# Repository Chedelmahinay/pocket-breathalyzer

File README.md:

# iot-project

### Conventional Commits

In this project, **Conventional Commits** are used, which is a simple set of rules to structure and create an explicit commit history that is easy to read both for humans and machines if needed.

Learn more about describing the features, fixes, and breaking changes made in commit messages here: [Click Me](https://www.conventionalcommits.org/en/v1.0.0/#specification)

#### The commit message should be structured as follows:
```<type>(scope): <description>```

#### The commit contains the following structural elements:

- **fix**: a commit of the ```type``` ___fix___ patches a bug in your codebase.

- **feat**: a commit of the ```type``` ___feat___ introduces a new feature to the codebase.

- **!**: a commit that appends a ___!___ after the ```scope```, introduces a ___breaking change___. A breaking change can be part of commits of any type.

#### Examples:

Commit message with ```!``` to draw attention to a ___breaking change___:

- ```feat(api)!: send an email to the customer when a product is shipped```

Commit message with ```scope``` lang:

- ```feat(lang): add Polish language```

Commit message with ```type``` fix:

- ```fix(ui): css syntax error```

### Branching Strategy

A **branching strategy** is a set of rules or guidelines that development teams use to manage the process of writing, merging, and deploying code with the help of a version control system like **Git**. It defines how developers interact with a shared codebase.

Strategies like these are essential as they help in keeping project repositories organized, error-free, and **avoid the unwanted merge conflicts** when multiple developers simultaneously push and pull code from the same repository.

To learn more about branching strategies: [Click Me](https://www.geeksforgeeks.org/git/branching-strategies-in-git/)

A _modified_ version of the **GitLab Flow** is used in this project.

#### GitLab Flow (modified):

The types of branches that can be present in GitFlow are:

- **master/main**: Main production branch housing stable release ready code.

- **dev**: Contains new features and bug fixes. This branch is used to combine new features and bug fixes for the release. Upon completion, developers merge the changes from the ```dev``` branch into the ```main/master``` branches.

- **feature/<scope<d>>**: Developers initiate ```feature/*``` branch from the ```dev``` branch to implement new features or address bugs. Upon completion, they integrate the changes from the ```feature/*``` branch into the ```dev``` branch. **For example:**
    - ```feature/ui```: To work on the UI of the project
    - ```feature/api```: To work on the API calls of the project

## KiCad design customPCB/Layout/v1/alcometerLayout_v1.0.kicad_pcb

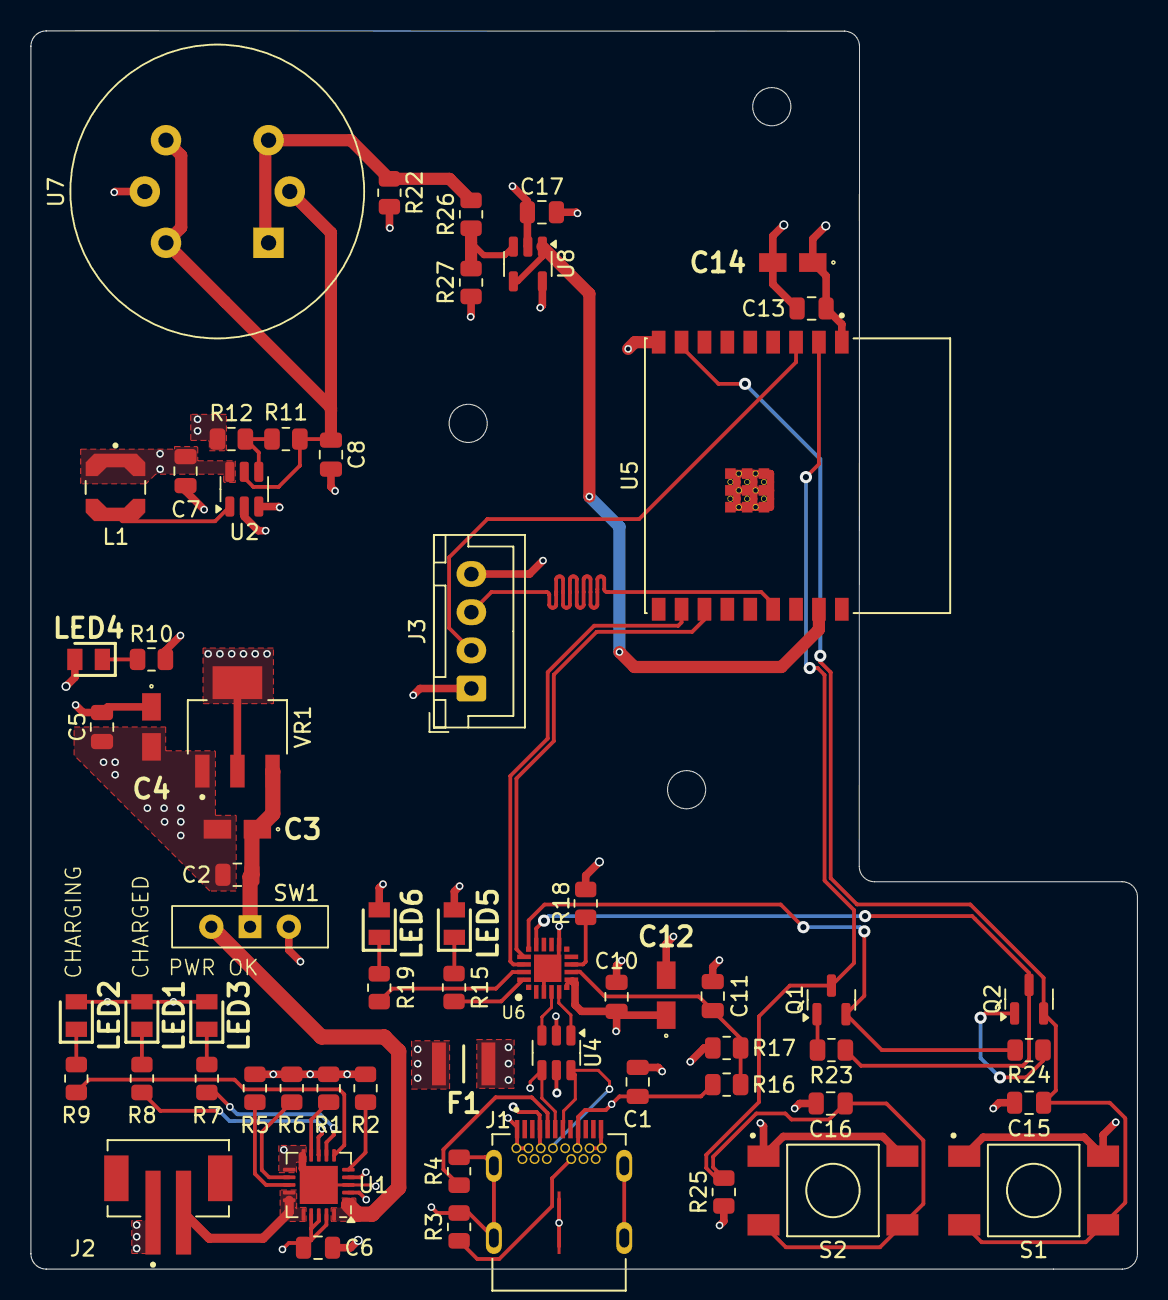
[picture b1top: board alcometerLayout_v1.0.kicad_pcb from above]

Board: 4 copper layers, 72.5 x 81.1 mm, 63 parts (0 on the bottom side), 44 nets.

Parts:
C1, C2, C5, C10, C13, C15: 0.1uF; C_0805_2012Metric
C3, C4, C14: 10uF; T491A
C6, C11, C16: 1uF; C_0805_2012Metric
C7: 4.7uF; C_0805_2012Metric
C8: 10uF; C_0805_2012Metric
C12: 4.7uF; T491A
C17: 100nF; C_0805_2012Metric
F1: 0ZCH0110AF2E; FUSC3226X100N
J1: SS-52400-003; BELFUSE_SS-52400-003
J2: B2B-PH-SM4-TB; JST_B2B-PH-SM4-TB
J3: Conn_01x04_Pin; JST_XH_B4B-XH-A_1x04_P2.50mm_Vertical
L1: 4.7uH; IND_LPS4018-472MRC
LED1, LED5: LTST-C170GKT; LEDC2012X120N
LED2, LED4, LED6: LTST-C170KRKT; LEDC2012X120N
LED3: LTST-C170TBKT; LEDC2012X120N
Q1, Q2: BC817; SOT-23
R1, R2, R23, R24, R25, R27: 10K; R_0805_2012Metric
R3, R4, R26: 5K1; R_0805_2012Metric
R5: 2K; R_0805_2012Metric
R6: 20K; R_0805_2012Metric
R7, R8, R9, R10, R15, R19: 470; R_0805_2012Metric
R11: 976; R_0805_2012Metric
R12: 309; R_0805_2012Metric
R16: 22K1; R_0805_2012Metric
R17: 47K5; R_0805_2012Metric
R18, R22: 1K; R_0805_2012Metric
S1, S2: FSM4JSMAATR; SW_FSM4JSMAATR
SW1: SW_Wuerth_450301014042; SW_Slide-03_Wuerth-WS-SLTV_10x2.5x6.4_P2.54mm
U1: MCP73871; QFN-20-1EP_4x4mm_P0.5mm_EP2.5x2.5mm
U2: MCP1640Bx-xCHY; SOT-23-6
U4: USBLC6-2SC6; SOT-23-6
U5: ESP32-C3-WROOM-02-H4; MODULE_ESP32-C3-WROOM-02-H4
U6: CP2102N-A02-GQFN20; WFQFN-20
U7: MQ-3; MQ-6
U8: MCP6001R; SOT-23-5
VR1: LM1117MPX-3.3; VREG_LM1117MPX-3.3

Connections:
+3V3: C4.1, C5.1, C7.1, C10.1, C12.1, C13.1, C14.1, C17.1, J3.1, L1.1, LED4.2 (A), LED5.2 (A), LED6.2 (A), R18.1, R25.1, U2.3 (EN), U2.6 (V_{IN}), U5.1 (3V3), U6.6 (VDD), U6.7 (VREGIN), U8.2 (V+), VR1.2 (VOUT_2), VR1.4 (VOUT_4)
+5V: C2.1, C3.1, C8.1, R11.1, SW1.1 (B), SW1.3 (A), U1.1 (OUT), U1.20 (OUT), U2.5 (V_{OUT}), U7.2 (VH+), U7.4 (A2), U7.6 (A1), VR1.3 (VIN)
/+5V_USB: C6.1, F1.2, LED1.2 (A), LED2.2 (A), LED3.2 (A), U1.2 (VPCC), U1.4 (PROG2), U1.17 (CE), U1.18 (IN), U1.19 (IN)
/CHARGED: R8.1, U1.8 (STAT1/~LBO)
/CHARGING: R9.1, U1.6 (~PG)
/CHARGING_POWER_GOOD: R7.1, U1.7 (STAT2)
/ESP32-C6-MINI-1/+3V3_ADC: U5.17 (IO1), U8.1, U8.4 (-)
/ESP32-C6-MINI-1/BOOT: C15.1, Q2.2 (E), S1.3, S1.4, U5.8 (IO9)
/ESP32-C6-MINI-1/DTR: Q2.3 (C), R23.1, U6.15 (CTS)
/ESP32-C6-MINI-1/EN: C16.1, Q1.3 (C), R25.2, S2.3, S2.4, U5.2 (EN)
/ESP32-C6-MINI-1/RTS: Q1.2 (E), R24.1, U6.16 (RTS)
/ESP32-C6-MINI-1/RX_TX: U5.12 (TXD), U6.17 (RXD)
/ESP32-C6-MINI-1/SCL: J3.3, U5.15 (IO3)
/ESP32-C6-MINI-1/SDA: J3.2, U5.3 (IO4)
/ESP32-C6-MINI-1/Sensors/+5V_ADC: R22.1, R26.1, U7.1 (B1), U7.3 (B2)
/ESP32-C6-MINI-1/TX_RX: U5.11 (RXD), U6.18 (TXD)
/ESP32-C6-MINI-1/USB_D+: U4.3 (I/O2), U6.4 (D+)
/ESP32-C6-MINI-1/USB_D-: U4.1 (I/O1), U6.5 (D-)
/PWD_LED: LED4.1 (K), R10.2
/USB_DN: J1.A7 (DN1), J1.B7 (DN2), U4.6 (I/O1)
/USB_DP: J1.A6 (DP1), J1.B6 (DP2), U4.4 (I/O2)
/VBAT: J2.2, U1.14 (V_{BAT}), U1.15 (V_{BAT}), U1.16 (V_{BAT_SENSE})
/VBUS: C1.1, F1.1, J1.A4 (VBUSA1), J1.A9 (VBUSA2), J1.B4 (VBUSB1), J1.B9 (VBUSB2), R16.1, U4.5 (VBUS)
GND: C1.2, C2.2, C3.2, C4.2, C5.2, C6.2, C7.2, C8.2, C10.2, C11.2, C12.2, C13.2, C14.2, C15.2, C16.2, C17.2, J1.A1 (GNDA1), J1.A12 (GNDA2), J1.B1 (GNDB1), J1.B12 (GNDB2), J1.G1 (GND/SHIELD), J1.G2 (GND/SHIELD), J1.G3 (GND/SHIELD), J1.G4 (GND/SHIELD), J1.S1 (GND/SHIELD), J1.S2 (GND/SHIELD), J1.S3 (GND/SHIELD), J1.S4 (GND/SHIELD), J2.1, J3.4, R1.2, R2.2, R3.2, R4.2, R5.2, R6.2, R10.1, R12.2, R17.2, R22.2, R27.2, S1.1, S1.2, S2.1, S2.2, SW1.2 (C), U1.3 (SEL), U1.10 (V_{SS}), U1.11 (V_{SS}), U1.21 (V_{SS}), U2.2 (GND), U4.2 (GND), U5.9 (GND), U5.19 (GND), U5.20 (GND), U5.21 (GND), U5.22 (GND), U5.23 (GND), U5.24 (GND), U5.25 (GND), U5.26 (GND), U5.27 (GND), U5.28 (GND), U5.29 (GND), U5.30 (GND), U5.31 (GND), U5.32 (GND), U5.33 (GND), U5.34 (GND), U5.35 (GND), U5.36 (GND), U5.37 (GND), U5.38 (GND), U5.39 (GND), U6.3 (GND), U6.12 (GND), U6.EXP (GND), U7.5 (VH-), U8.5 (V-), VR1.1 (GND)
unnamed: J1.A5 (CC1), R4.1
unnamed: J1.B5 (CC2), R3.1
unnamed: LED1.1 (K), R8.2
unnamed: LED2.1 (K), R9.2
unnamed: LED3.1 (K), R7.2
unnamed: LED5.1 (K), R15.2
unnamed: LED6.1 (K), R19.2
unnamed: Q1.1 (B), R23.2
unnamed: Q2.1 (B), R24.2
unnamed: R5.1, U1.13 (PROG1)
unnamed: R6.1, U1.12 (PROG3)
unnamed: R2.1, U1.5 (THERM)
unnamed: R1.1, U1.9 (~TE)
unnamed: L1.2, U2.1 (SW)
unnamed: R11.2, R12.1, U2.4 (V_{FB})
unnamed: R15.1, U6.20 (GPIO2/TXT)
unnamed: R19.1, U6.19 (GPIO3/RXT)
unnamed: R18.2, U6.9 (RSTB)
unnamed: C11.1, R16.2, R17.1, U6.8 (VBUS)
unnamed: R26.2, R27.1, U8.3 (+)

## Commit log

2025-11-11 fix(readme): change readme
2025-11-12 Configure SAST in `.gitlab-ci.yml`, creating this file if it does not already exist
2025-11-22 project creation and supabase connection
2025-11-25 Documentation(readme): Add Project overview and task scaling
2025-11-25 fix(gitignore): add .env.local
2025-11-25 package-lock.json
2025-11-30 feat(username): added username option to signup and updated it to be shown instead of email
2025-11-30 feat(ui): protectedPage initial commit
2025-12-11 feat(ble): BLE test
2025-12-16 feat(ui): landingPage initial commit + Hero section edited/in progress
2025-12-18 feat(ui): redesigned page + added user guide + project description
2025-12-22 modulated landingPage files + removed unused files + refactored margin/padding & text contents in section
2025-12-23 feat(idf): test ble w/ esp idf
2025-12-24 feat(ble): add barebone ble functionality
2025-12-28 feat(ble): add reconnection & manual disconnect & delete hello_world example
2025-12-28 vercel test
2025-12-28 Remove node_modules from repository
2025-12-28 Remove node_modules committed by mistake
2025-12-28 Removed deploy button
2025-12-28 chore: remove accidental root-level npm files
2025-12-28 test: Repo mirroring
2025-12-28 test: Repo
2025-12-29 modification: Modified settings for vercel
2025-12-29 update: Updated next for vercel
2026-01-04 feat(adc)!: barebone adc1 measuring w/ ble on
2026-01-04 fix(gitignore): gitignore fix lol
2026-01-11 feat(user info page): Added user info page. Modification possibility needs to be added and ui changes
2026-01-11 feat(user info page): vercel test
2026-01-12 feat(sensor): delete b profile(ble) & convert adc to bac & send bac to client
2026-01-14 fix(esp32): build files. must add them to .gitignore later
2026-01-14 fix(gitignore): add esp idf build files into .gitignore
2026-01-18 feat(display): rework OLED display and add SSD1306 driver with isolated RTOS task for test
2026-01-20 update(display): add static oled screen displays. navigation logic pending
2026-01-20 feature(button): add test working navigation button
2026-01-20 update(main): add working main.c for test
2026-01-22 fix(ui): show only highest BAC
2026-01-25 feat(user info page): first working version
2026-01-26 feat(nvs): create nvs folder & CMakeLists edit
2026-01-27 feat: button-driven OLED menu with inverted START/RESULTS
2026-01-28 feat(user info page): added links to profile page
2026-01-29 feat(nvs): save last highest result to NVS
2026-02-03 feat(ranking page): currently showing user history. Needs to be fixed
2026-02-05 feat(password change): added pwd change option
2026-02-05 feat(weekly ranking): added a table showing weekly result from every user
2026-02-07 add button two function feat, add bitmap batt,mq3ble w temp placeholders
2026-02-07 clean up non-functional lines
2026-02-08 feat(buttons): centralize GPIO config and task start in buttons_init()
2026-02-09 fix(build): fucking build files
2026-02-12 fix(gitignore): ignore build files
2026-02-17 feat(ui fixes): ui fixes and added gender option to profiles
2026-02-20 feat(ai chat bot): Initial version of the ai chat bot. Gives responses based on the user data from supabase.
2026-02-20 feat(landing): add nav link to user BAC measurements
2026-02-23 feat(ui changes): New ui design ideas for mobile
2026-03-01 feat(oled): add live BAC display in start option via ADC fanout task(ADC logic inside .c unchanged)
2026-03-03 feat(ui changes): Hamburger menu for mobile
2026-03-03 feat(ui changes): Hamburger menu changes
2026-03-03 feat(ui changes): ui fixes to light mode
2026-03-03 fix(ui): show all values again; used to be only the higher one
2026-03-03 fix(uart): mg/ml --> promille
2026-03-03 fix(lcd): bigger font
2026-03-03 fix(ui): centering the font
2026-03-05 fix(uart): user breath time from 7 sec to 4sec
2026-03-08 refactor(ui/buttons): improve debounce button task + simplify OLED task + and clean main module
2026-03-09 feat(ui changes): litle ui tweaks
2026-03-10 feat(pwa): adding manifest.json
2026-03-10 feat(oled/results): results screen, remove avg display, store last 3 test BAC peaks
2026-03-10 refactor(oled): clean up display code and remove unused static functions
2026-03-10 Revert "Merge branch 'feature/oled-btns' into 'main'"
    This reverts merge request !1
2026-03-11 feat(utc fix): Fixed the timestamp to show finlands time utc+2
2026-03-12 feat(manifest): added manifest. pwa not working
2026-03-13 files(pcb): 3d model, schematics & layout
2026-03-15 feat(utc fix): Fixed the timestamp to show finlands time utc+2 and small ui fixes
2026-03-15 Add new directory
2026-03-15 Breathalyzer case Top+down part
2026-03-15 Breathalyzer Buttons and bottom stands
